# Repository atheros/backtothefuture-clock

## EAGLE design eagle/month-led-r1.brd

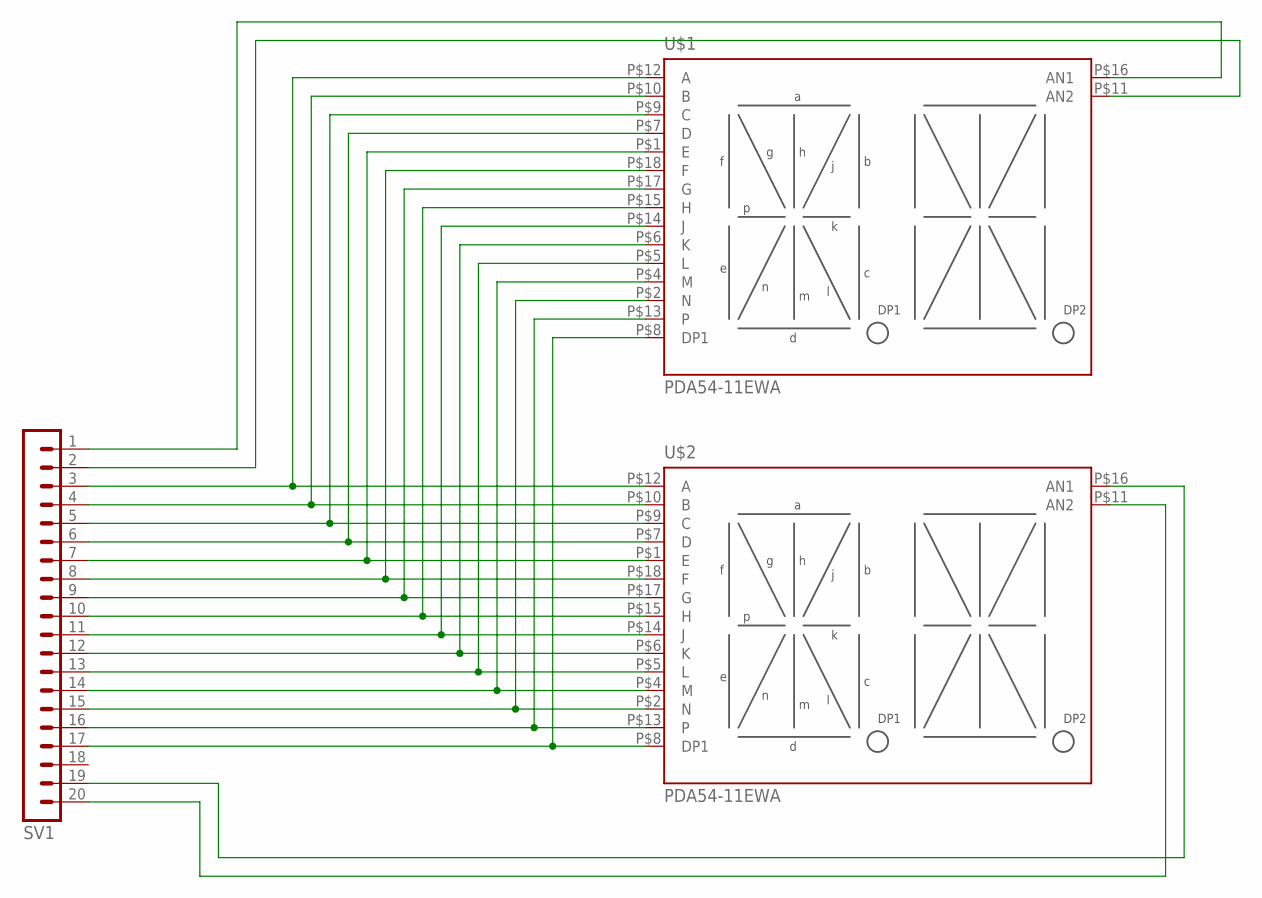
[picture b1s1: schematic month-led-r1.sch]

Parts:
SV1: MA20-1W
U$1, U$2: PDA54-11EWA; PDA54-11XX

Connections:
unnamed: SV1.3, U$1.P$12 (A), U$2.P$12 (A)
unnamed: SV1.4, U$1.P$10 (B), U$2.P$10 (B)
unnamed: SV1.5, U$1.P$9 (C), U$2.P$9 (C)
unnamed: SV1.6, U$1.P$7 (D), U$2.P$7 (D)
unnamed: SV1.7, U$1.P$1 (E), U$2.P$1 (E)
unnamed: SV1.8, U$1.P$18 (F), U$2.P$18 (F)
unnamed: SV1.9, U$1.P$17 (G), U$2.P$17 (G)
unnamed: SV1.10, U$1.P$15 (H), U$2.P$15 (H)
unnamed: SV1.11, U$1.P$14 (J), U$2.P$14 (J)
unnamed: SV1.12, U$1.P$6 (K), U$2.P$6 (K)
unnamed: SV1.13, U$1.P$5 (L), U$2.P$5 (L)
unnamed: SV1.14, U$1.P$4 (M), U$2.P$4 (M)
unnamed: SV1.15, U$1.P$2 (N), U$2.P$2 (N)
unnamed: SV1.16, U$1.P$13, U$2.P$13
unnamed: SV1.17, U$1.P$8 (DP1), U$2.P$8 (DP1)
unnamed: SV1.2, U$1.P$11 (AN2)
unnamed: SV1.19, U$2.P$16 (AN1)
unnamed: SV1.20, U$2.P$11 (AN2)
unnamed: SV1.1, U$1.P$16 (AN1)

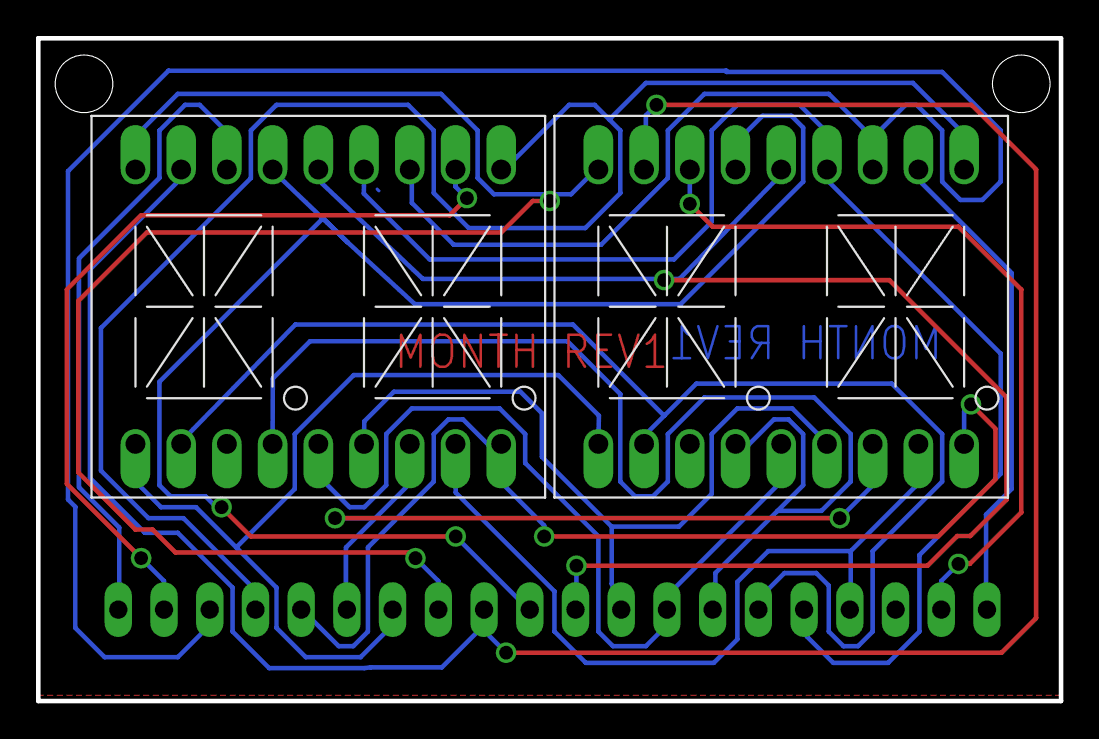
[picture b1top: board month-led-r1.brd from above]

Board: 2 copper layers, 56.8 x 36.8 mm, 3 parts (1 on the bottom side), 19 nets.

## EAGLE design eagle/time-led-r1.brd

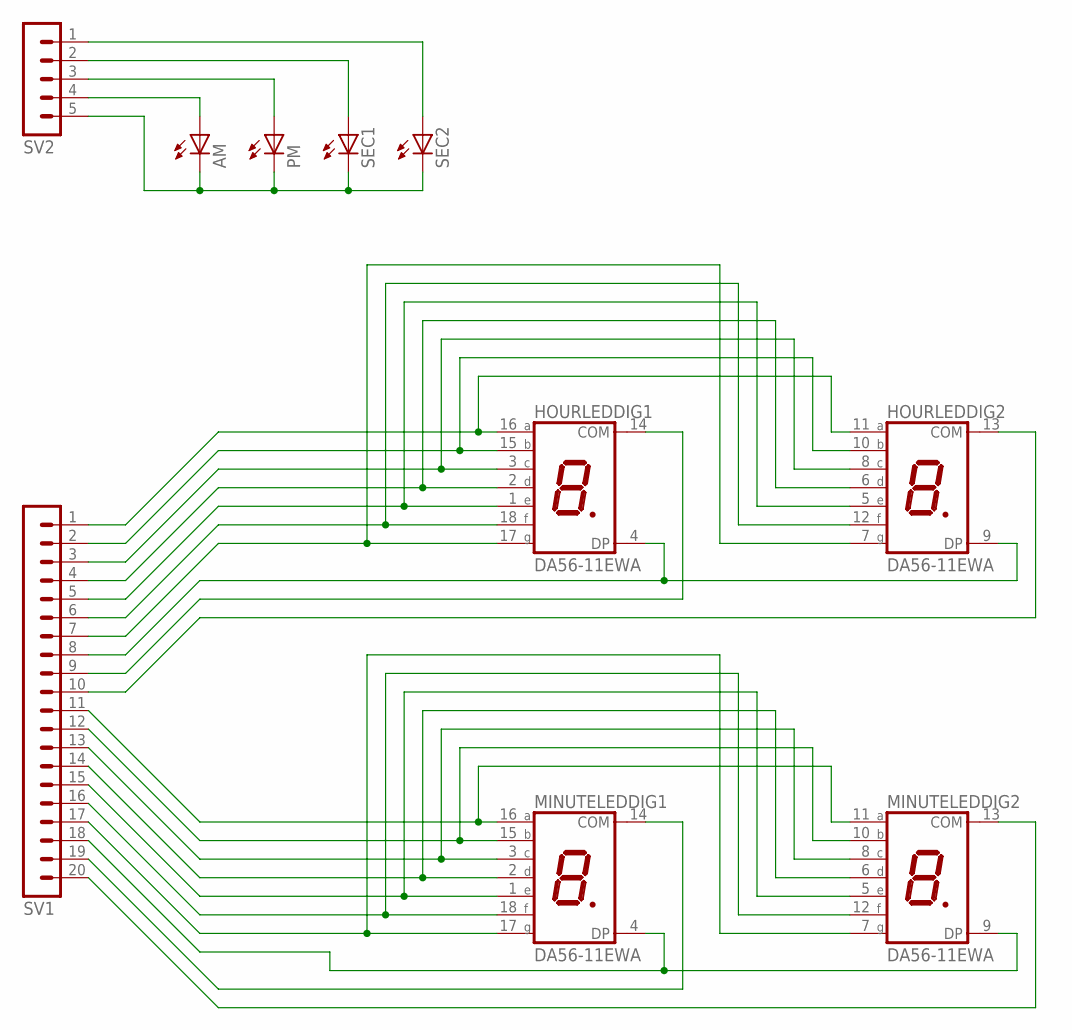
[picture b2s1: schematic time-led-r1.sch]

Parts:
AM: LED3MM
HOURLED: DA56-11EWA; DA56
MINUTELED: DA56-11EWA; DA56
PM: LED3MM
SEC1, SEC2: LED3MM
SV1: MA20-1W
SV2: MA05-1

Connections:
unnamed: HOURLED.11 (A), HOURLED.16 (A), SV1.1
unnamed: HOURLED.10 (B), HOURLED.15 (B), SV1.2
unnamed: HOURLED.3 (C), HOURLED.8 (C), SV1.3
unnamed: HOURLED.2 (D), HOURLED.6 (D), SV1.4
unnamed: HOURLED.1 (E), HOURLED.5 (E), SV1.5
unnamed: HOURLED.12 (F), HOURLED.18 (F), SV1.6
unnamed: HOURLED.7 (G), HOURLED.17 (G), SV1.7
unnamed: HOURLED.4 (DP), HOURLED.9 (DP), SV1.8
unnamed: MINUTELED.11 (A), MINUTELED.16 (A), SV1.11
unnamed: MINUTELED.10 (B), MINUTELED.15 (B), SV1.12
unnamed: MINUTELED.3 (C), MINUTELED.8 (C), SV1.13
unnamed: MINUTELED.2 (D), MINUTELED.6 (D), SV1.14
unnamed: MINUTELED.1 (E), MINUTELED.5 (E), SV1.15
unnamed: MINUTELED.12 (F), MINUTELED.18 (F), SV1.16
unnamed: MINUTELED.7 (G), MINUTELED.17 (G), SV1.17
unnamed: MINUTELED.4 (DP), MINUTELED.9 (DP), SV1.18
unnamed: HOURLED.13 (COM), SV1.10
unnamed: AM.K (C), PM.K (C), SEC1.K (C), SEC2.K (C), SV2.5
unnamed: HOURLED.14 (COM), SV1.9
unnamed: AM.A, SV2.4
unnamed: PM.A, SV2.3
unnamed: SEC1.A, SV2.2
unnamed: SEC2.A, SV2.1
unnamed: MINUTELED.14 (COM), SV1.19
unnamed: MINUTELED.13 (COM), SV1.20

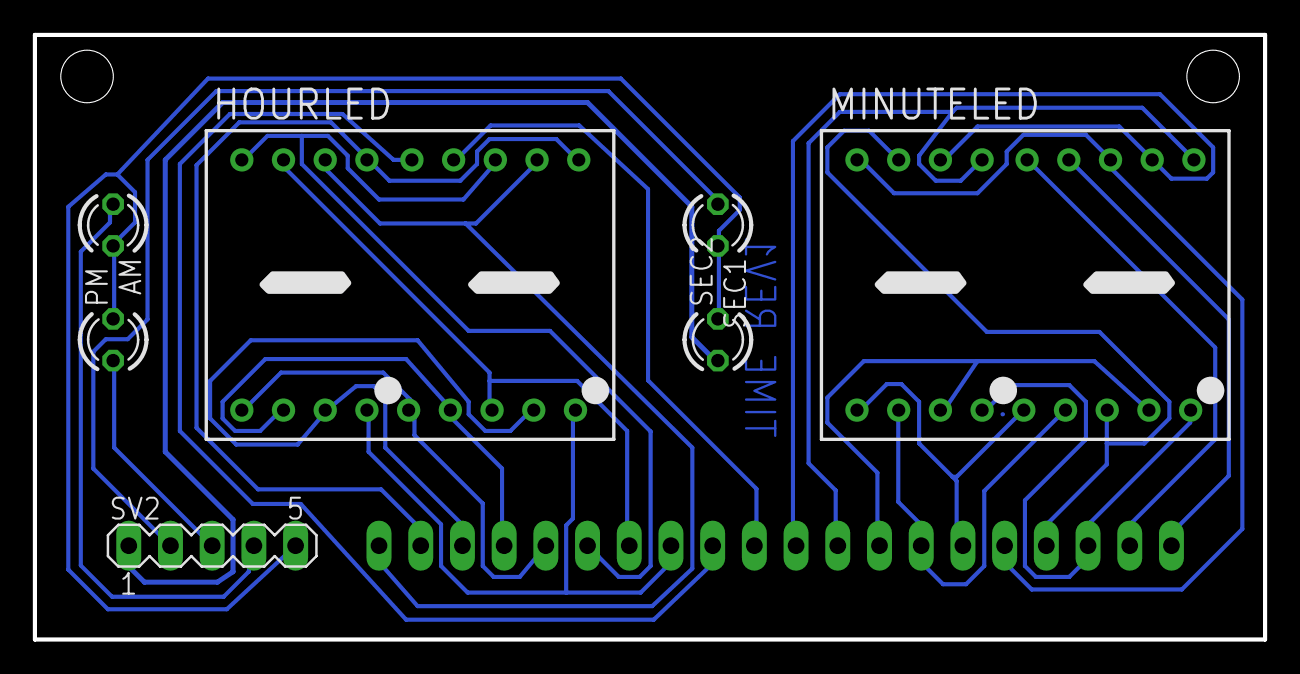
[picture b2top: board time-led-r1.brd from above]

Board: 2 copper layers, 74.9 x 36.8 mm, 8 parts (1 on the bottom side), 25 nets.

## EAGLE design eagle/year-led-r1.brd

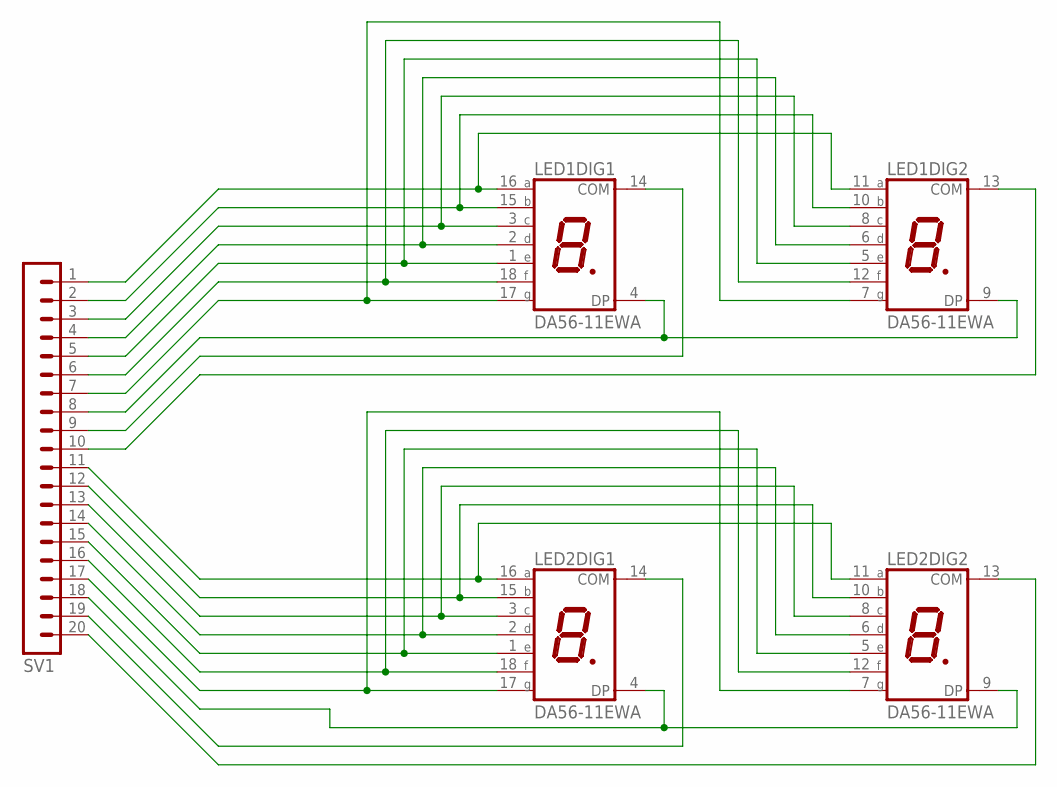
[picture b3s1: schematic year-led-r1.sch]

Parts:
LED1, LED2: DA56-11EWA; DA56
SV1: MA20-1W

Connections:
unnamed: LED1.11 (A), LED1.16 (A), SV1.1
unnamed: LED1.10 (B), LED1.15 (B), SV1.2
unnamed: LED1.3 (C), LED1.8 (C), SV1.3
unnamed: LED1.2 (D), LED1.6 (D), SV1.4
unnamed: LED1.1 (E), LED1.5 (E), SV1.5
unnamed: LED1.12 (F), LED1.18 (F), SV1.6
unnamed: LED1.7 (G), LED1.17 (G), SV1.7
unnamed: LED1.4 (DP), LED1.9 (DP), SV1.8
unnamed: LED2.11 (A), LED2.16 (A), SV1.11
unnamed: LED2.10 (B), LED2.15 (B), SV1.12
unnamed: LED2.3 (C), LED2.8 (C), SV1.13
unnamed: LED2.2 (D), LED2.6 (D), SV1.14
unnamed: LED2.1 (E), LED2.5 (E), SV1.15
unnamed: LED2.12 (F), LED2.18 (F), SV1.16
unnamed: LED2.7 (G), LED2.17 (G), SV1.17
unnamed: LED2.4 (DP), LED2.9 (DP), SV1.18
unnamed: LED1.13 (COM), SV1.10
unnamed: LED1.14 (COM), SV1.9
unnamed: LED2.14 (COM), SV1.19
unnamed: LED2.13 (COM), SV1.20

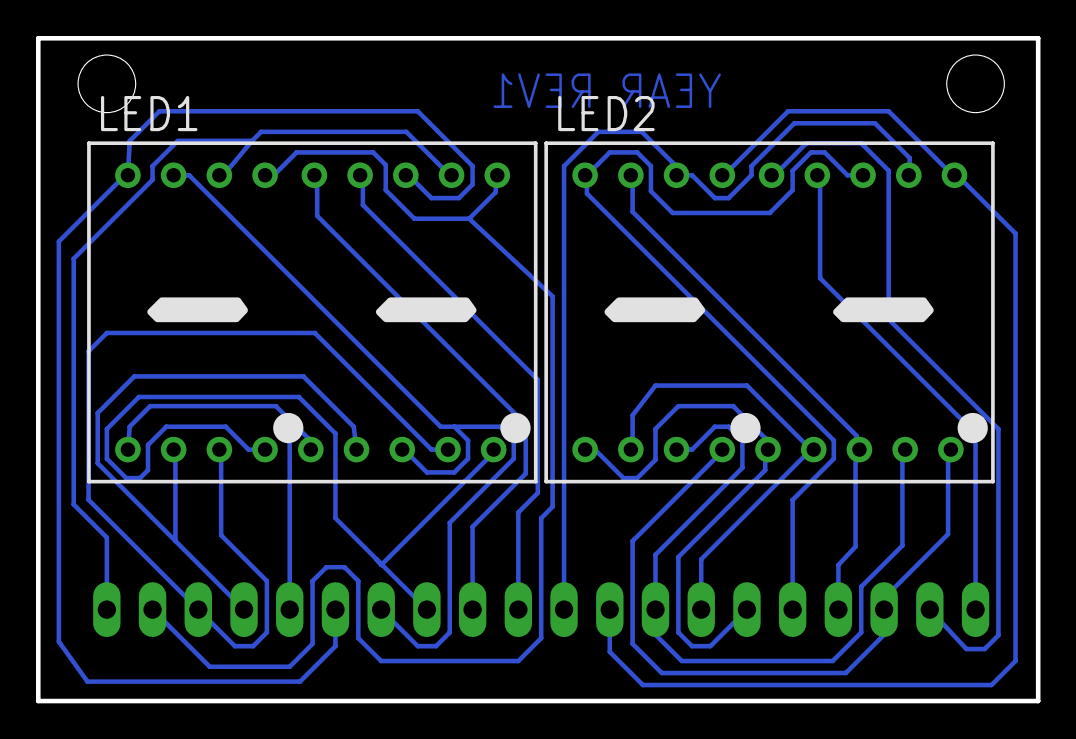
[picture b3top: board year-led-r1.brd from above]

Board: 2 copper layers, 55.5 x 36.8 mm, 3 parts (1 on the bottom side), 20 nets.

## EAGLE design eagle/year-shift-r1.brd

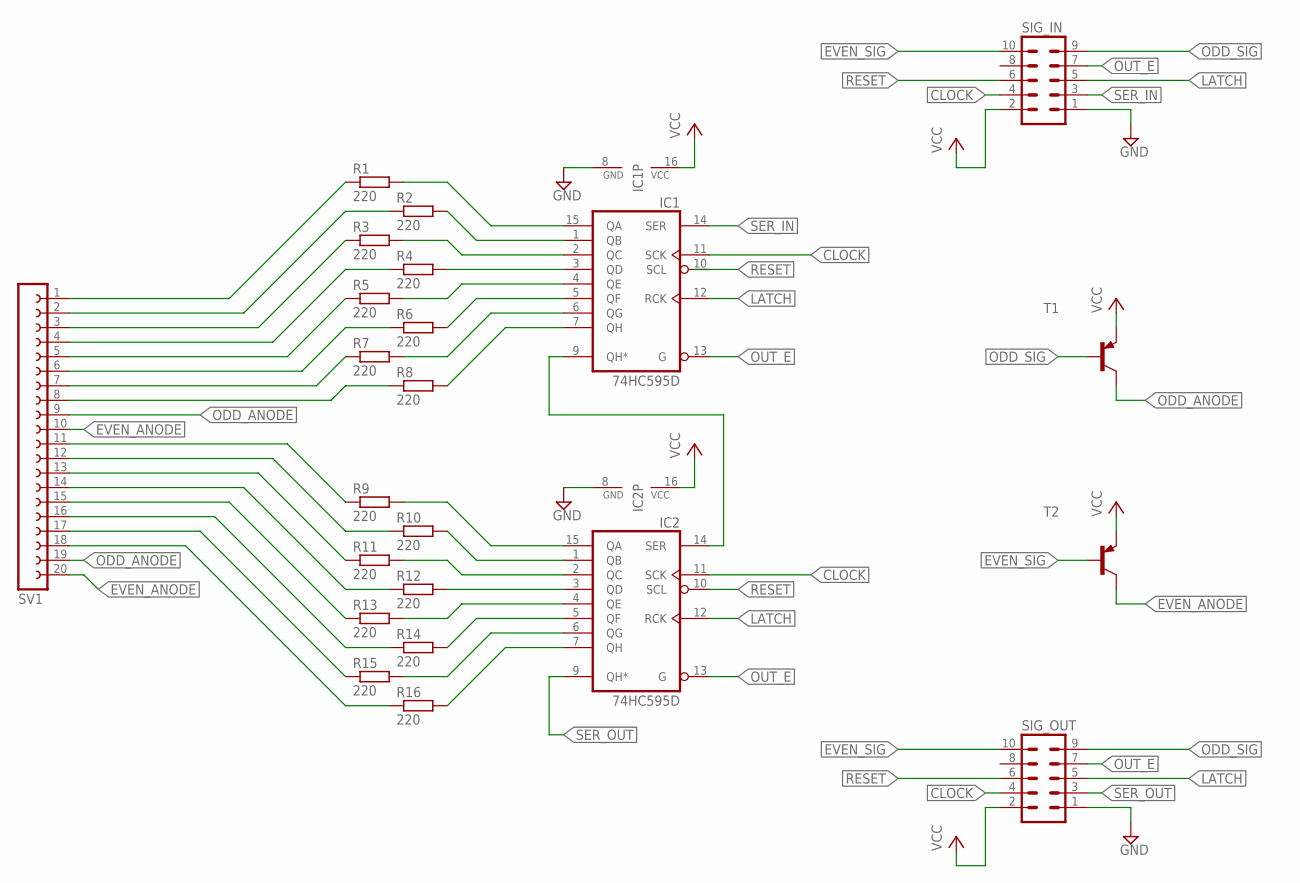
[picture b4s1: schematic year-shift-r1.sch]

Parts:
IC1, IC2: 74HC595D; SO16
R1, R2, R3, R4, R5, R6, R7, R8, R9, R10, R11, R12, R13, R14, R15, R16: 220; R0805
SIG_IN: MA05-2
SIG_OUT: MA05-2
SV1: FE20-1; FE20
T1, T2: BC557B-PNP-TO92-EBC; TO92-EBC

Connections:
CLOCK: IC1.11 (SCK), IC2.11 (SCK), SIG_IN.4, SIG_OUT.4
EVEN_ANODE: SV1.10, SV1.20, T2.C
EVEN_SIG: SIG_IN.10, SIG_OUT.10, T2.B
GND: IC1.8 (GND), IC2.8 (GND), SIG_IN.1, SIG_OUT.1
LATCH: IC1.12 (RCK), IC2.12 (RCK), SIG_IN.5, SIG_OUT.5
unnamed: IC1.15 (QA), R1.2
unnamed: IC1.2 (QC), R3.2
unnamed: IC1.4 (QE), R5.2
unnamed: IC1.6 (QG), R7.2
unnamed: R8.1, SV1.8
unnamed: R6.1, SV1.6
unnamed: R4.1, SV1.4
unnamed: R2.1, SV1.2
unnamed: IC1.1 (QB), R2.2
unnamed: IC1.3 (QD), R4.2
unnamed: IC1.5 (QF), R6.2
unnamed: IC1.7 (QH), R8.2
unnamed: IC2.15 (QA), R9.2
unnamed: IC2.2 (QC), R11.2
unnamed: IC2.4 (QE), R13.2
unnamed: IC2.6 (QG), R15.2
unnamed: R16.1, SV1.18
unnamed: R14.1, SV1.16
unnamed: R12.1, SV1.14
unnamed: R10.1, SV1.12
unnamed: IC2.1 (QB), R10.2
unnamed: IC2.3 (QD), R12.2
unnamed: IC2.5 (QF), R14.2
unnamed: IC2.7 (QH), R16.2
unnamed: IC1.9 (QH*), IC2.14 (SER)
unnamed: R1.1, SV1.1
unnamed: R3.1, SV1.3
unnamed: R5.1, SV1.5
unnamed: R7.1, SV1.7
unnamed: R9.1, SV1.11
unnamed: R11.1, SV1.13
unnamed: R13.1, SV1.15
unnamed: R15.1, SV1.17
ODD_ANODE: SV1.9, SV1.19, T1.C
ODD_SIG: SIG_IN.9, SIG_OUT.9, T1.B
OUT_E: IC1.13 (G), IC2.13 (G), SIG_IN.7, SIG_OUT.7
RESET: IC2.10 (SCL), SIG_IN.6, SIG_OUT.6
SER_IN: IC1.14 (SER), SIG_IN.3
SER_OUT: IC2.9 (QH*), SIG_OUT.3
VCC: IC1.16 (VCC), IC2.16 (VCC), SIG_IN.2, SIG_OUT.2, T1.E, T2.E

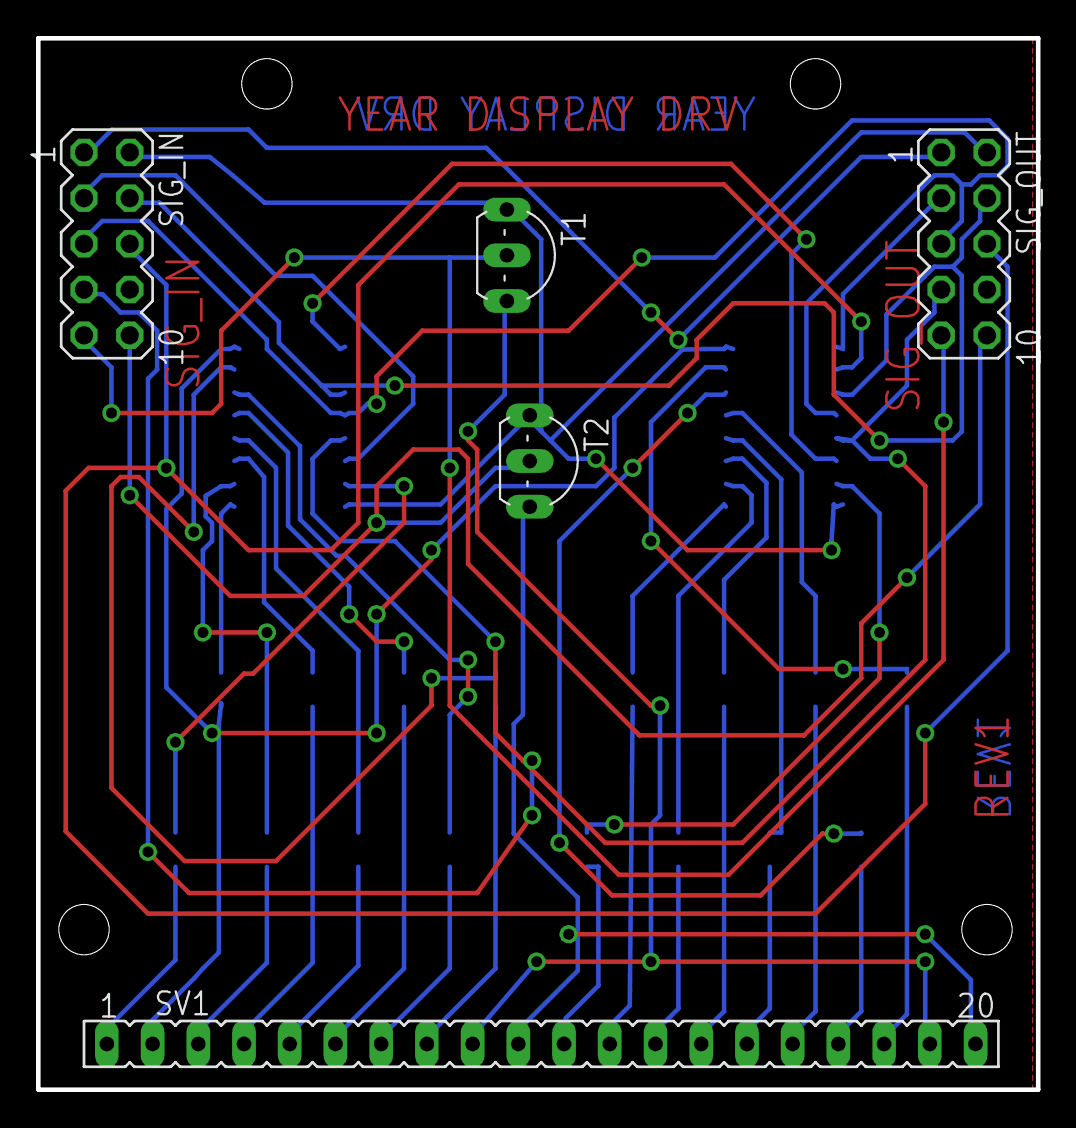
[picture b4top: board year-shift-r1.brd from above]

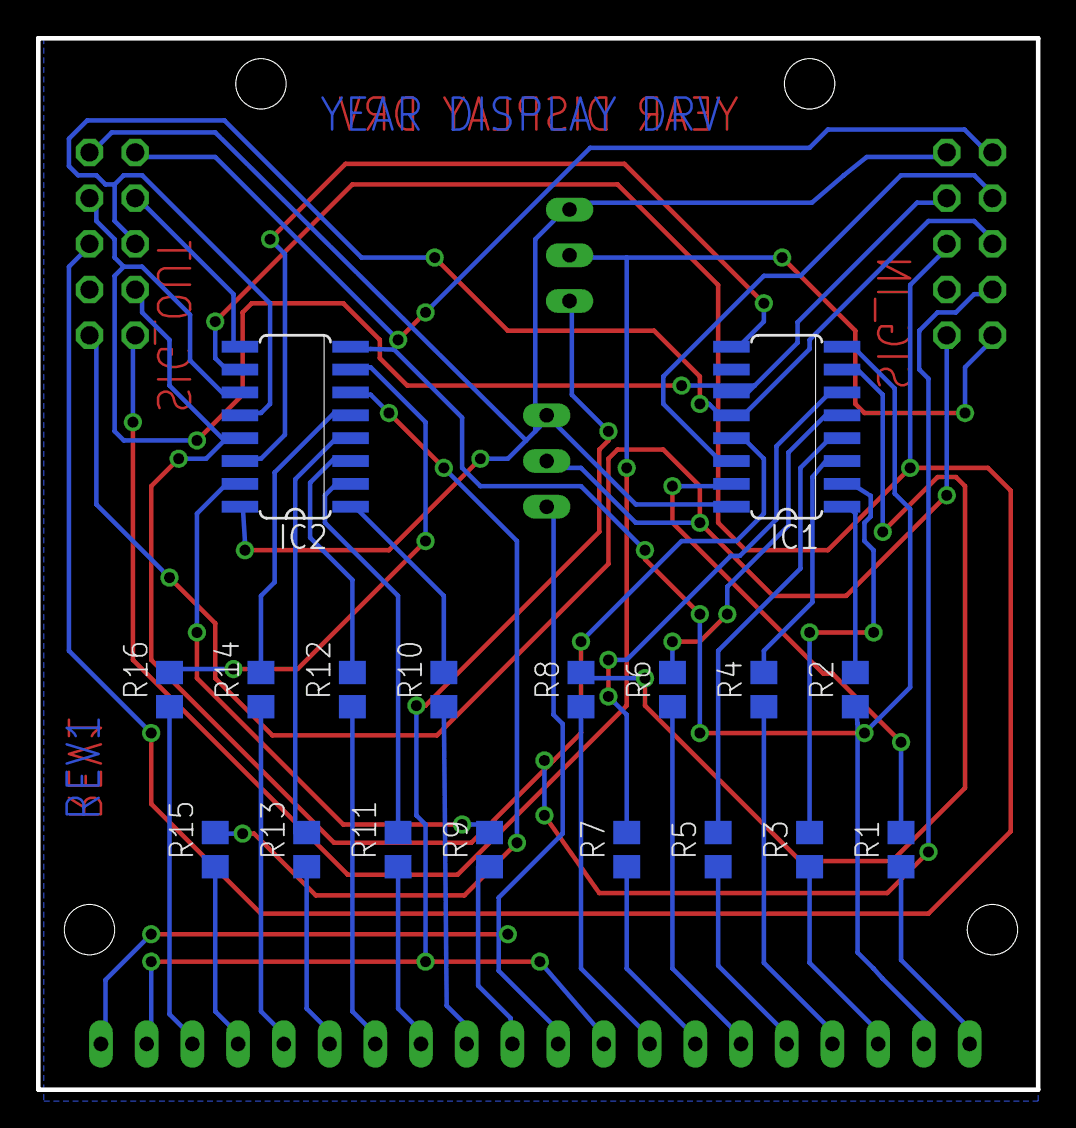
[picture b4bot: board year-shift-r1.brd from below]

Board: 2 copper layers, 55.5 x 58.4 mm, 23 parts (18 on the bottom side), 45 nets.

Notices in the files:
parts and their libraries:
eagle-library-edeca.net-v5: This is v1 and is licensed under the Creative Commons (Attribution-Non-Commercial-Share Alike 2.0 UK)
